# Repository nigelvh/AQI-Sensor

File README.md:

# AQI Sensor
Custom hardware for measuring the Air Quality Index along with environmental Temperature, Pressure, and Humidity. [Read more about the project here!](https://digitalnigel.com/wordpress/?p=3436)

## Hardware
The PCB designs for the device, as well as a STL for the 3D printed portion of the enclosure.

## Firmware
The firmware I run on my devices, written for MicroPython.

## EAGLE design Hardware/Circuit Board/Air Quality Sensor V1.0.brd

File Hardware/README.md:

# AQI Sensor Hardware
This is a custom board for interfacing an ESP32 microcontroller with a pair of Plantower PMS7003 particulate sensors, and a Bosch Sensortec BME280 Temperature, Pressure, and Humidity sensor.

The hardware was designed, along with a 3D printed carrier, to mount inside a 3" PVC pipe cap for a simple and inexpensive outdoor enclosure. It should be noted that the design requires use of a 3" PVC pipe cap with a domed end. The flat face pipe caps will not let the board and carrier seat fully.

## Circuit Board
The schematic and board files have been created in Eagle, though I cannot guarantee how they will load without all of the associated libraries. The gerber files are also provided which can be sent directly to a PCB fab house. Additionally there are exported images of the schematic and board designs for review without using the Eagle CAD software.

A parts text file has been included to cover some of the more important, or more specific, parts used in the design. It is not all inclusive (I didn't include the passives for example), but it covers the main components.

## 3D Print
The board is designed to fit into a 3D printed carrier, and mount into a 3" PVC pipe cap to form the outdoor enclosure. I have printed these in PETG which was chosen for its properties when exposed to the elements. Your choices may differ.

The carrier was modelled in FreeCAD, but the STL has been provided as well to import directly into your slicer of choice.

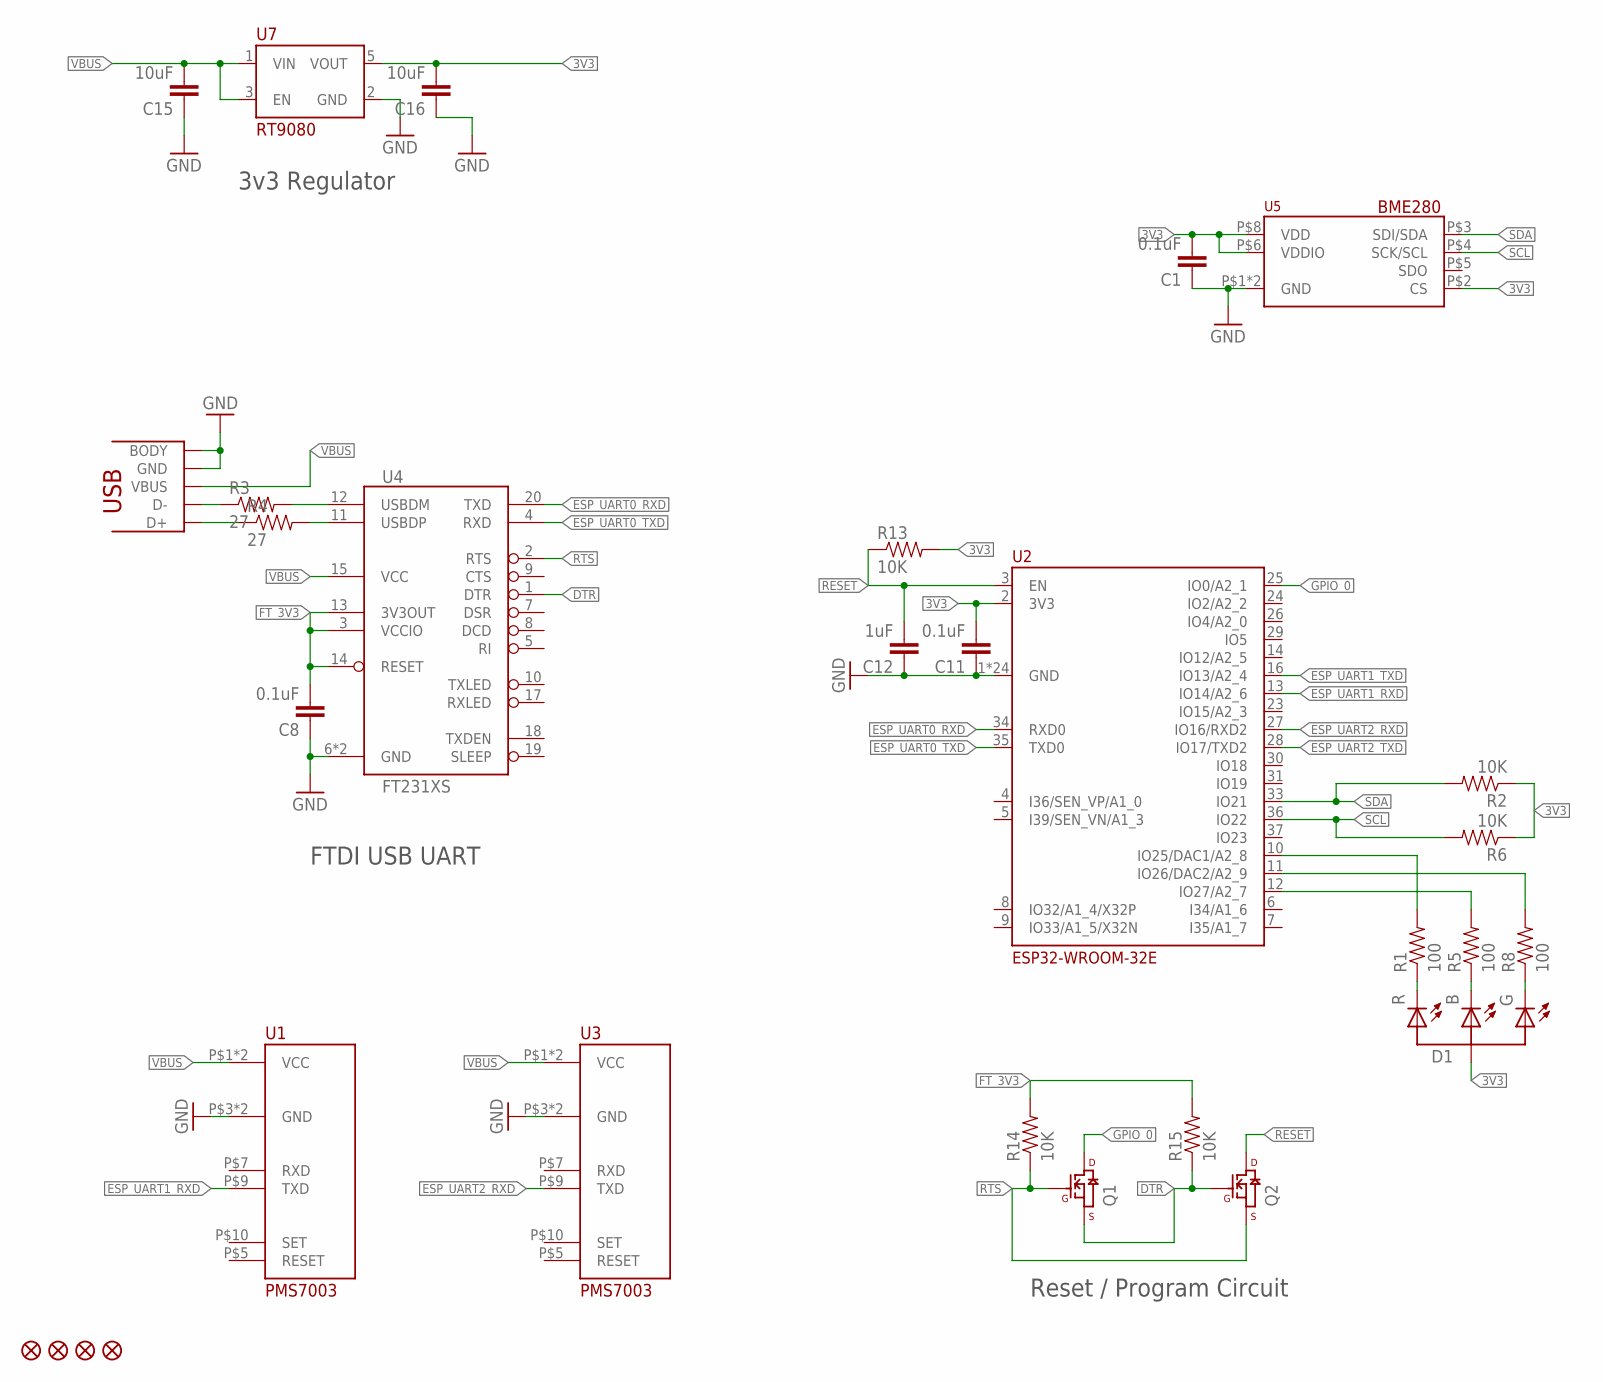
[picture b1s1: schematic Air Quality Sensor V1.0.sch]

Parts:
C1, C8, C11: 0.1uF; 0603-CAP
C12: 1uF; 0603-CAP
C15, C16: 10uF; 1206
D1: LED_TRICOLOR_COM-ANODE; LED_1206_SIDE_TRICOLOR
FID1, FID2, FID3, FID4: FIDUCIAL
Q1, Q2: MOSFET_N_CHANNELSI1308; SC-70-3
R1, R5, R8: 100; 0603-RES
R2, R6, R13, R14, R15: 10K; 0603-RES
R3, R4: 27; 0603-RES
U1, U3: PMS7003_SMD
U2: ESP32-WROOM-32E
U4: FT231XS; SSOP-20
U5: BME280; 8-VFLGA
U7: RT9080; SOT-23-5
U$1: USB-MICROB; USB-MICROB-10118192

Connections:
3V3: C1.2, C11.2, C16.2, D1.P$3 (A), R2.1, R6.1, R13.2, U2.2 (3V3), U5.P$2 (CS), U5.P$6 (VDDIO), U5.P$8 (VDD), U7.5 (VOUT)
DTR: Q1.P$2 (S), Q2.P$1 (G), R15.1, U4.1 (DTR)
ESP_UART0_RXD: U2.34 (RXD0), U4.20 (TXD)
ESP_UART0_TXD: U2.35 (TXD0), U4.4 (RXD)
ESP_UART1_RXD: U1.P$9 (TXD), U2.13 (IO14/A2_6)
ESP_UART1_TXD: U2.16 (IO13/A2_4)
ESP_UART2_RXD: U2.27 (IO16/RXD2), U3.P$9 (TXD)
ESP_UART2_TXD: U2.28 (IO17/TXD2)
FT_3V3: C8.2, R14.2, R15.2, U4.3 (VCCIO), U4.13 (3V3OUT), U4.14 (RESET)
GND: C1.1, C8.1, C11.1, C12.1, C15.1, C16.1, U1.P$3 (GND), U1.P$4 (GND), U2.1 (GND), U2.15 (GND), U2.38 (GND), U2.P$1 (GND), U2.P$2 (GND), U2.P$3 (GND), U2.P$4 (GND), U2.P$5 (GND), U2.P$6 (GND), U2.P$7 (GND), U2.P$8 (GND), U2.P$9 (GND), U2.P$10 (GND), U2.P$11 (GND), U2.P$12 (GND), U2.PAD@1 (GND), U2.PAD@2 (GND), U2.PAD@3 (GND), U2.PAD@4 (GND), U2.PAD@5 (GND), U2.PAD@6 (GND), U2.PAD@7 (GND), U2.PAD@8 (GND), U2.PAD@9 (GND), U3.P$3 (GND), U3.P$4 (GND), U4.6 (GND), U4.16 (GND), U5.P$1 (GND), U5.P$7 (GND), U7.2 (GND), U$1.5 (GND), U$1.BODY@1 (BODY), U$1.BODY@2 (BODY), U$1.BODY@3 (BODY), U$1.BODY@4 (BODY), U$1.BODY@5 (BODY), U$1.BODY@6 (BODY)
GPIO_0: Q1.P$3 (D), U2.25 (IO0/A2_1)
unnamed: R1.2, U2.10 (IO25/DAC1/A2_8)
unnamed: R8.2, U2.11 (IO26/DAC2/A2_9)
unnamed: R5.2, U2.12 (IO27/A2_7)
unnamed: D1.P$4 (C_RED), R1.1
unnamed: D1.P$2 (C_BLU), R5.1
unnamed: D1.P$1 (C_GRN), R8.1
unnamed: R3.1, U$1.2 (D-)
unnamed: R4.1, U$1.3 (D+)
unnamed: R4.2, U4.11 (USBDP)
unnamed: R3.2, U4.12 (USBDM)
RESET: C12.2, Q2.P$3 (D), R13.1, U2.3 (EN)
RTS: Q1.P$1 (G), Q2.P$2 (S), R14.1, U4.2 (RTS)
SCL: R6.2, U2.36 (IO22), U5.P$4 (SCK/SCL)
SDA: R2.2, U2.33 (IO21), U5.P$3 (SDI/SDA)
VBUS: C15.2, U1.P$1 (VCC), U1.P$2 (VCC), U3.P$1 (VCC), U3.P$2 (VCC), U4.15 (VCC), U7.1 (VIN), U7.3 (EN), U$1.1 (VBUS)

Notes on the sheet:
FTDI USB UART
3v3 Regulator
Reset / Program Circuit

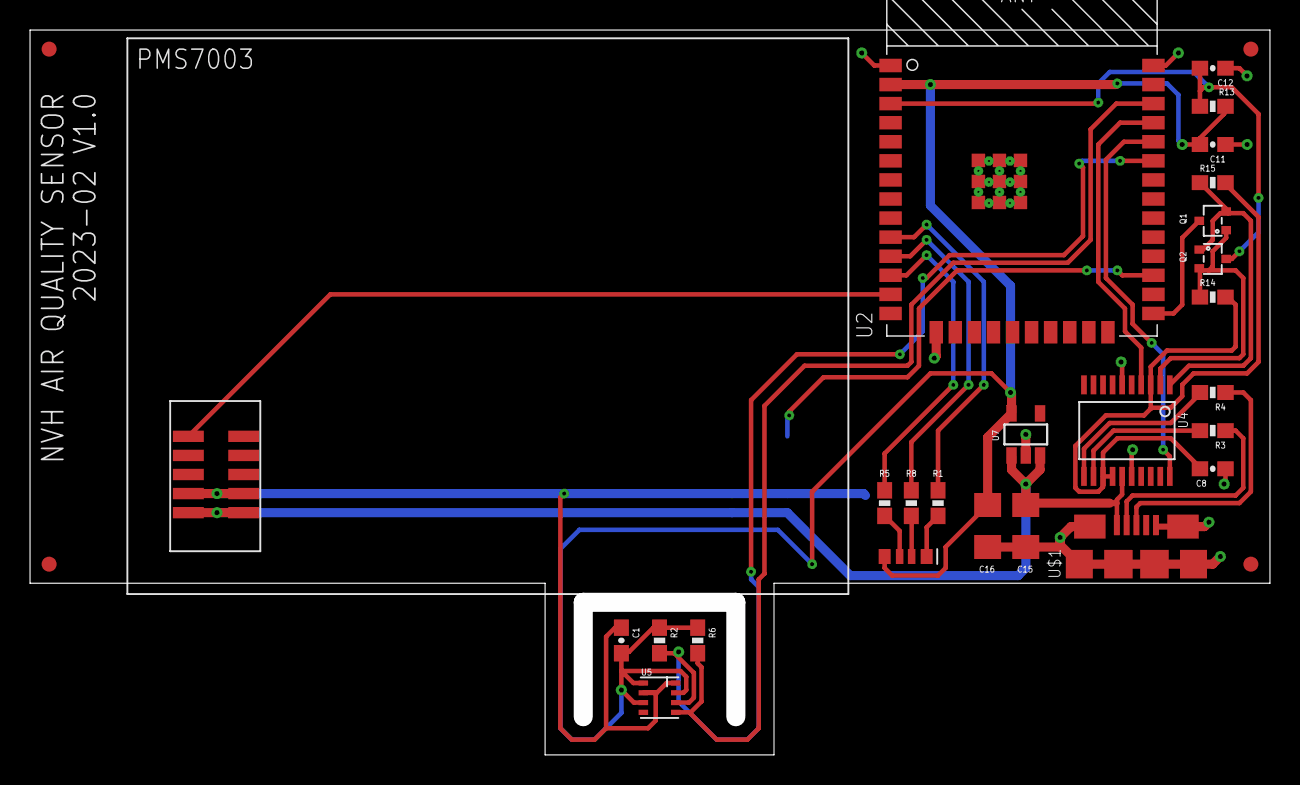
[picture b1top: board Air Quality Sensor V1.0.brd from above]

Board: 2 copper layers, 81.3 x 47.0 mm, 30 parts (1 on the bottom side), 24 nets.

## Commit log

2023-03-04 Initial README.md
2023-03-04 Add .gitignore.
2023-03-04 Add Hardware directory, along with the board files, and 3d model for the carrier.
2023-03-04 Initial commit of all the code. Slight tweak for hardware readme.
2023-03-04 Slight README tweaks.
2023-03-04 Readme update to include post link.
2023-03-04 Update README to reference the Firmware folder.
2024-10-11 Better error handling in cases where we don't have the particulate sensors installed.

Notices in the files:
parts and their libraries:
SparkFun: Licensing: CC v3.0 Share-Alike You are welcome to use this library for commercial purposes.
